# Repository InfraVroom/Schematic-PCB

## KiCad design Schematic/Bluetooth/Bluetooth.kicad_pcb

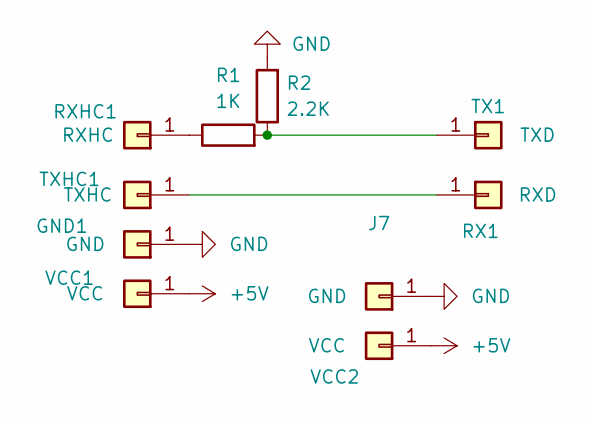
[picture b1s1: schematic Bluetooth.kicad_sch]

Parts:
GND1: GND; PinSocket_1x01_P1.27mm_Vertical
J7: GND; PinSocket_1x01_P1.27mm_Vertical
R1: 1K; R_Axial_DIN0204_L3.6mm_D1.6mm_P5.08mm_Horizontal
R2: 2.2K; R_Axial_DIN0204_L3.6mm_D1.6mm_P5.08mm_Horizontal
RX1: RXD; PinSocket_1x01_P1.27mm_Vertical
RXHC1: RXHC; PinSocket_1x01_P1.27mm_Vertical
TX1: TXD; PinSocket_1x01_P1.27mm_Vertical
TXHC1: TXHC; PinSocket_1x01_P1.27mm_Vertical
VCC1, VCC2: VCC; PinSocket_1x01_P1.27mm_Vertical

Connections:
+5V: VCC1.1, VCC2.1
GND: GND1.1, J7.1, R2.2
unnamed: RX1.1, TXHC1.1
unnamed: R1.1, RXHC1.1
unnamed: R1.2, R2.1, TX1.1

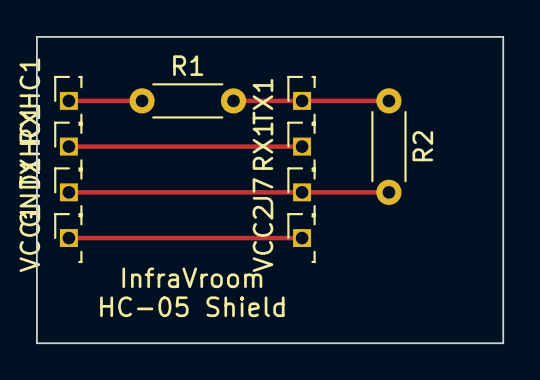
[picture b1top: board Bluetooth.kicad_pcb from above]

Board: 2 copper layers, 25.9 x 17.0 mm, 10 parts (0 on the bottom side), 5 nets.

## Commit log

2023-02-08 Schematic
2023-02-23 Updated schem
2023-03-10 Added BY Shield
